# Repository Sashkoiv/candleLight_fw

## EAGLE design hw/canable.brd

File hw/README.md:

# [CandleLightFirmware](https://wiki.linklayer.com/index.php/CandleLightFirmware)

# Flashing candleLight
* Flashing requires the dfu-util tool. On Ubuntu, this can be installed with `sudo apt install dfu-util`.
* Disconnect the USB connector from the board, short the BOOT pins, then reconnect the USB connector. The device should enumerate as "STM32 BOOTLOADER".
* Flash the device with: `sudo dfu-util --dfuse-address -d 0483:df11 -c 1 -i 0 -a 0 -s 0x08000000 -D gsusb_cantact_8b2b2b4.bin`
* Disconnect the USB connector, un-short the BOOT pins, and reconnect. The device is now flashed!

# Using candleLight
* Ensure the gs_usb kernel module is enabled: `sudo modprobe gs_usb`
* Configure the device: `sudo ip link set can0 type can bitrate 500000`. Replace can0 with the name of your device, and 500000 with the desired bitrate.
* Bring the device up: `sudo ifconfig can0 up`
* Use the device with SocketCAN. For example, `candump can0`. See SocketCAN for more information.

# Test
```sh
sudo ip link set can0 type can bitrate 500000
sudo ifconfig can0 up
candump can0
```
```sh
sudo ip link set can1 type can bitrate 500000
sudo ifconfig can1 up
cansend can1 123#DEADBEEF
```

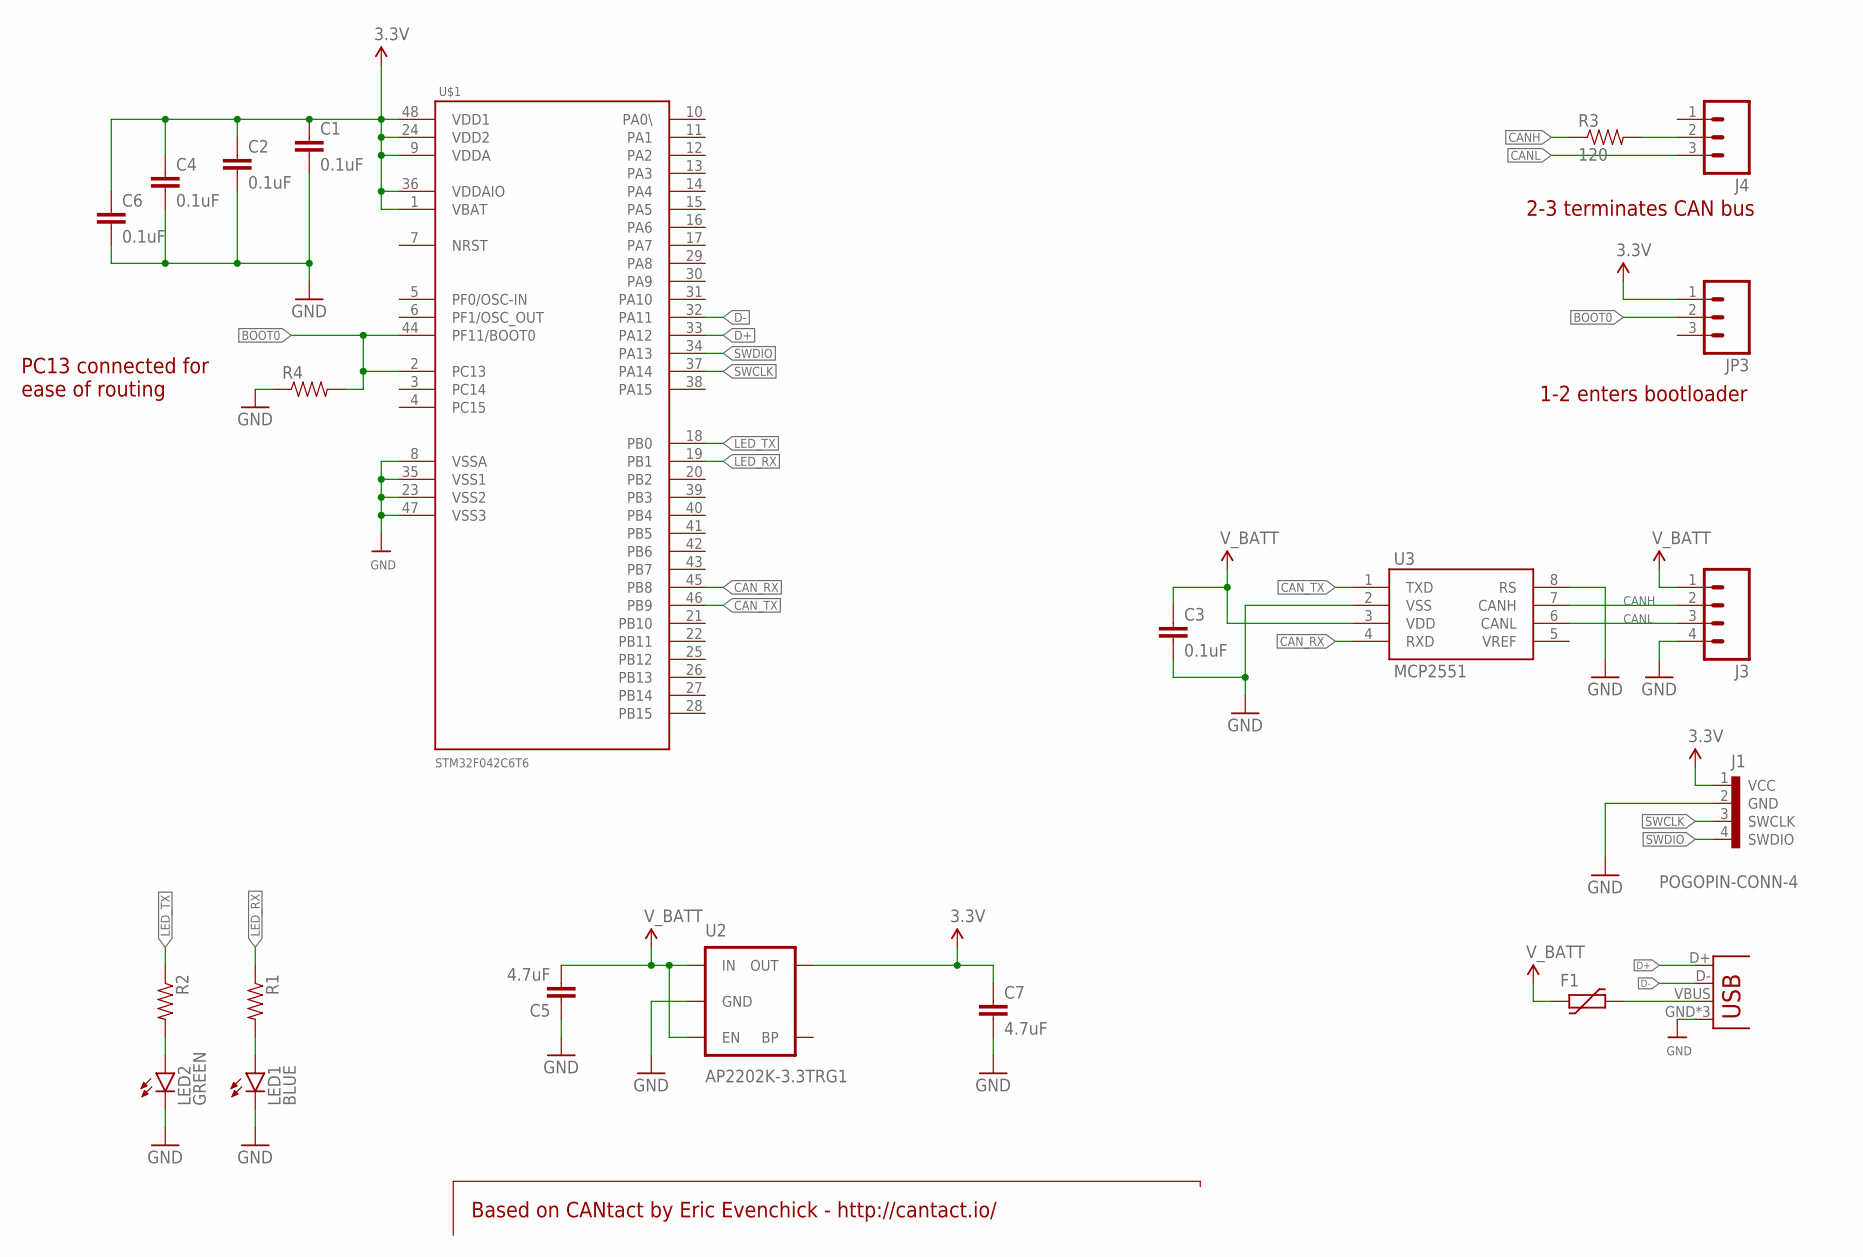
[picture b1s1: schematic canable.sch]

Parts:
C1, C2, C3, C4, C6: 0.1uF; 0603-CAP
C5, C7: 4.7uF; 0603-CAP
F1: FUSE_PTC-0805; PTC0805
J1: POGOPIN-CONN-4; POGOPROG-CONN-4-ALLSMT
J2: USB-MICROB
J3: M04SCREW_LOCK; SCREWTERMINAL-3.5MM-4_LOCK
J4: M03LOCK; 1X03_LOCK
JP3: M03LOCK; 1X03_LOCK
LED1: BLUE; LED-0603
LED2: GREEN; LED-0603
R1, R2, R4: RESISTOR0603-RES; 0603-RES
R3: 120; 0603-RES
U2: AP2202K-3.3TRG1; SOT23-5
U3: MCP2551; SO08
U$1: STM32F042C6T6; LQFP48

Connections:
3.3V: C1.1, C2.1, C4.1, C6.1, C7.1, J1.1 (VCC), JP3.1, U2.5 (OUT), U$1.1 (VBAT), U$1.9 (VDDA), U$1.24 (VDD2), U$1.36 (VDDAIO), U$1.48 (VDD1)
BOOT0: JP3.2, R4.2, U$1.2 (PC13), U$1.44 (PF11/BOOT0)
CANH: J3.2, R3.1, U3.7 (CANH)
CANL: J3.3, J4.3, U3.6 (CANL)
CAN_RX: U3.4 (RXD), U$1.45 (PB8)
CAN_TX: U3.1 (TXD), U$1.46 (PB9)
D+: J2.D+, U$1.33 (PA12)
D-: J2.D-, U$1.32 (PA11)
GND: C1.2, C2.2, C3.2, C4.2, C5.1, C6.2, C7.2, J1.2 (GND), J2.GND, J2.MT1 (GND), J2.MT2 (GND), J3.4, LED1.C, LED2.C, R4.1, U2.2 (GND), U3.2 (VSS), U3.8 (RS), U$1.8 (VSSA), U$1.23 (VSS2), U$1.35 (VSS1), U$1.47 (VSS3)
LED_RX: R1.1, U$1.19 (PB1)
LED_TX: R2.1, U$1.18 (PB0)
unnamed: LED2.A, R2.2
unnamed: J4.2, R3.2
unnamed: F1.2, J2.VBUS
unnamed: LED1.A, R1.2
SWCLK: J1.3 (SWCLK), U$1.37 (PA14)
SWDIO: J1.4 (SWDIO), U$1.34 (PA13)
V_BATT: C3.1, C5.2, F1.1, J3.1, U2.1 (IN), U2.3 (EN), U3.3 (VDD)

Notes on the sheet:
Based on CANtact by Eric Evenchick - http://cantact.io/
PC13 connected for ease of routing
2-3 terminates CAN bus
1-2 enters bootloader

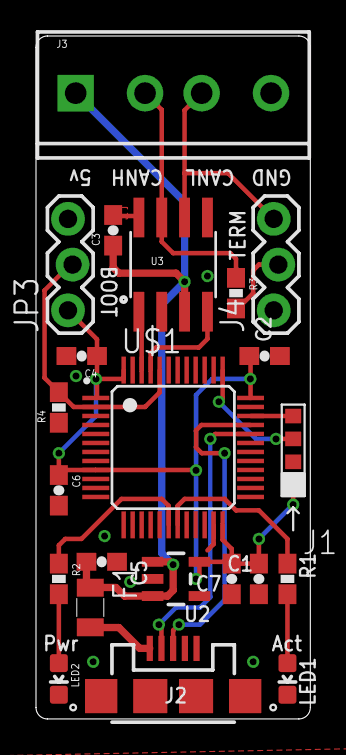
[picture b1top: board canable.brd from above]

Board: 2 copper layers, 15.2 x 37.9 mm, 23 parts (1 on the bottom side), 18 nets.

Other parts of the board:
U$3: CANABLE-0.2

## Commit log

2020-05-15 Add hardware files and binaries
    Small instruction note added.

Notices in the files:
parts and their libraries:
SparkFun-LED: Licensing: Creative Commons ShareAlike 4.0 International - https://creativecommons.org/licenses/by-sa/4.0
